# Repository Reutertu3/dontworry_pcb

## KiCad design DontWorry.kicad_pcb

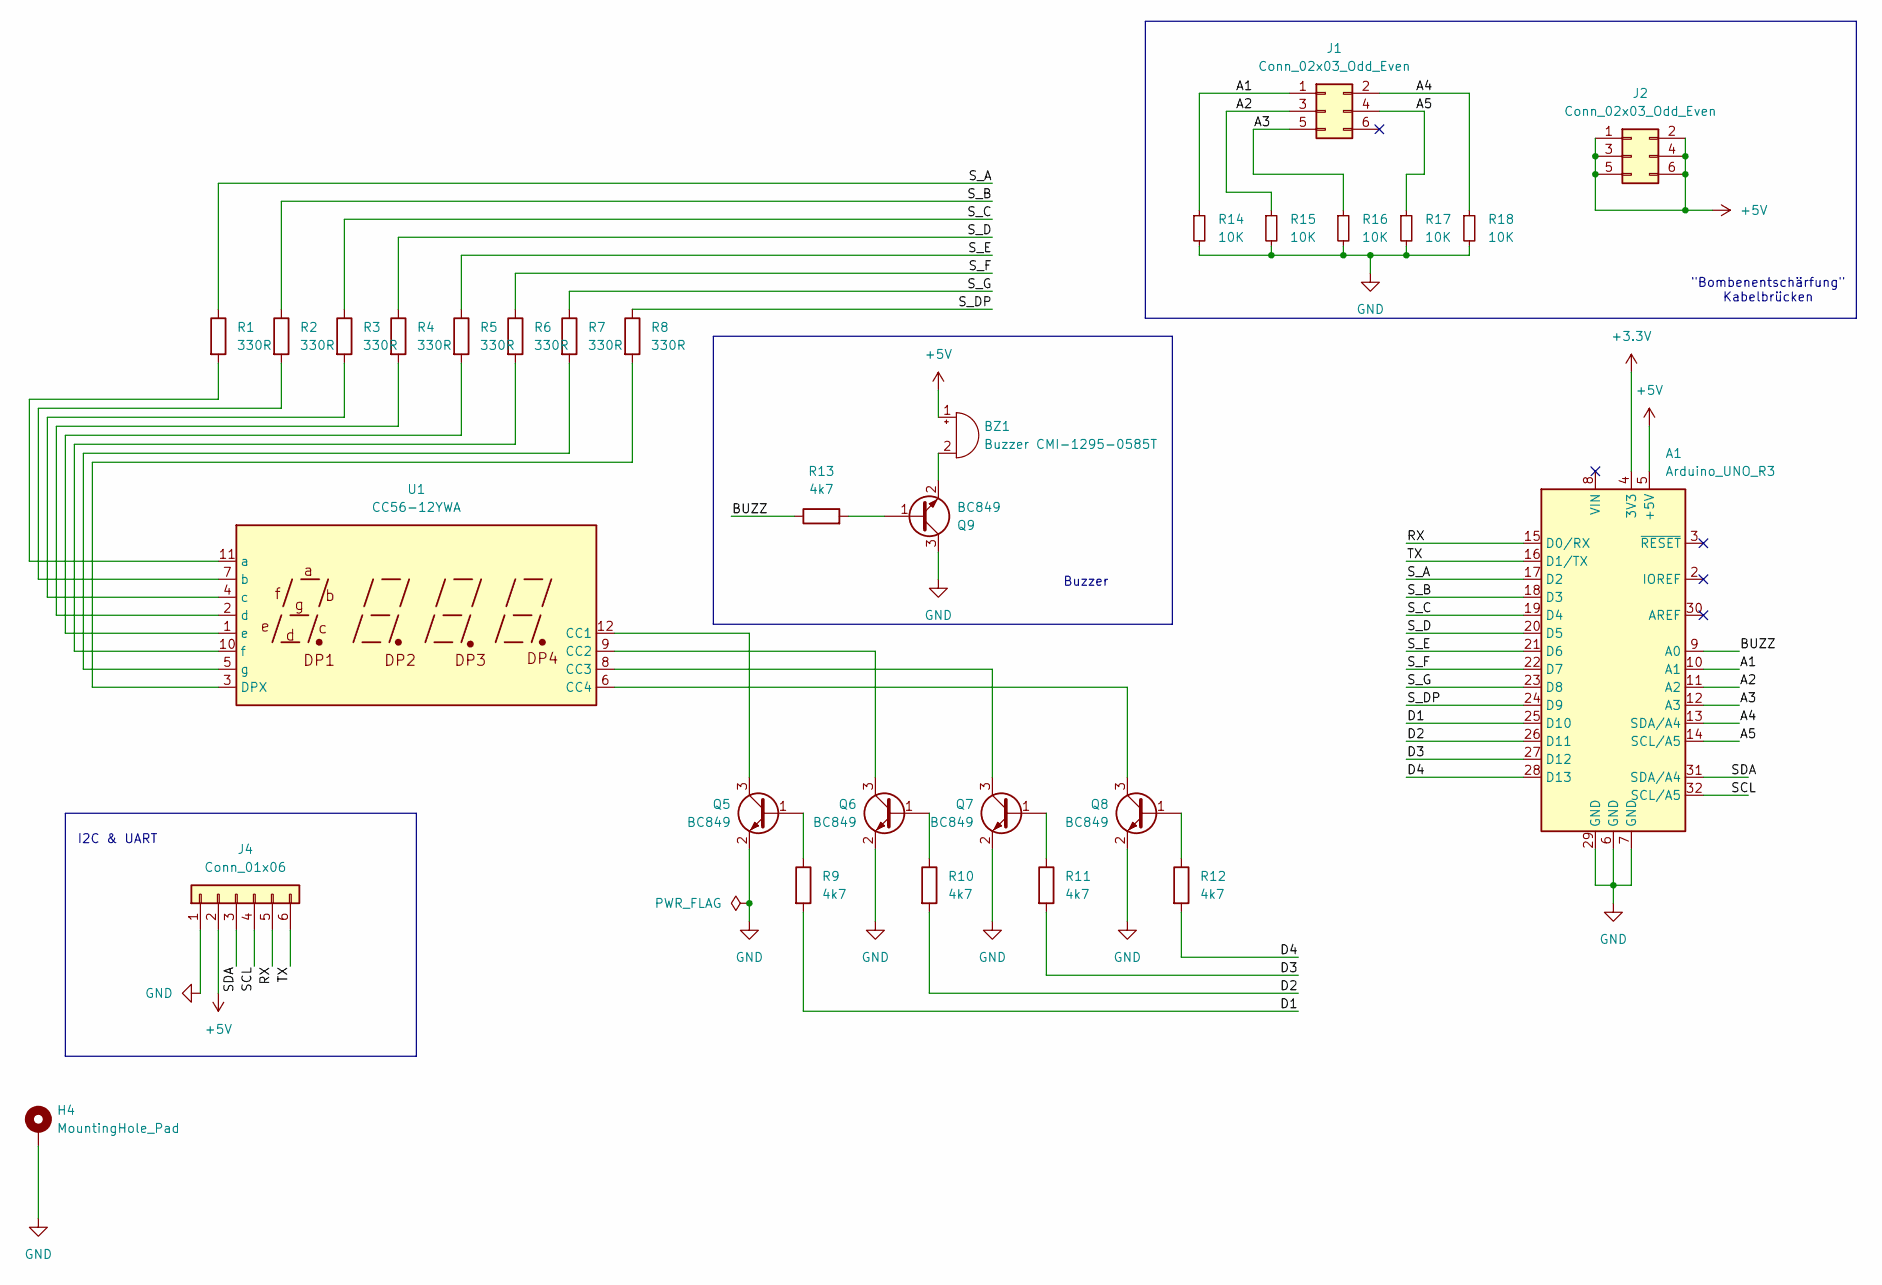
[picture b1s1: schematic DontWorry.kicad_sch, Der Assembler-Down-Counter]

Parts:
A1: Arduino_UNO_R3
BZ1: Buzzer CMI-1295-0585T; Buzzer_12x9.5RM7.6
H4: MountingHole_Pad; MountingHole_3.2mm_M3_DIN965_Pad
J1, J2: Conn_02x03_Odd_Even; PinHeader_2x03_P2.54mm_Vertical
J4: Conn_01x06; PinHeader_2x03_P2.54mm_Vertical
Q5, Q6, Q7, Q8, Q9: BC849; SOT-23
R1, R2, R3, R4, R5, R6, R7, R8: 330R; R_0805_2012Metric
R9, R10, R11, R12, R13: 4k7; R_0805_2012Metric
R14, R15, R16, R17, R18: 10K; R_0805_2012Metric
U1: CC56-12YWA

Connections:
+3.3V: A1.4 (3V3)
+5V: A1.5 (+5V), BZ1.1 (+), J2.1, J2.2, J2.3, J2.4, J2.5, J2.6, J4.2
/A1: A1.10 (A1), J1.1, R14.1
/A2: A1.11 (A2), J1.3, R15.1
/A3: A1.12 (A3), J1.5, R16.1
/A4: A1.13 (SDA/A4), J1.2, R18.1
/A5: A1.14 (SCL/A5), J1.4, R17.1
/BUZZ: A1.9 (A0), R13.1
/D1: A1.25 (D10), R9.2
/D2: A1.26 (D11), R10.2
/D3: A1.27 (D12), R11.2
/D4: A1.28 (D13), R12.2
/RX: A1.15 (D0/RX), J4.5
/SCL: A1.32 (SCL/A5), J4.4
/SDA: A1.31 (SDA/A4), J4.3
/S_A: A1.17 (D2), R1.1
/S_B: A1.18 (D3), R2.1
/S_C: A1.19 (D4), R3.1
/S_D: A1.20 (D5), R4.1
/S_DP: A1.24 (D9), R8.1
/S_E: A1.21 (D6), R5.1
/S_F: A1.22 (D7), R6.1
/S_G: A1.23 (D8), R7.1
/TX: A1.16 (D1/TX), J4.6
GND: A1.6 (GND), A1.7 (GND), A1.29 (GND), H4.1, J4.1, Q5.2 (E), Q6.2 (E), Q7.2 (E), Q8.2 (E), Q9.3 (C), R14.2, R15.2, R16.2, R17.2, R18.2
unnamed: BZ1.2 (-), Q9.2 (E)
unnamed: Q5.1 (B), R9.1
unnamed: Q5.3 (C), U1.12 (CC1)
unnamed: Q6.1 (B), R10.1
unnamed: Q6.3 (C), U1.9 (CC2)
unnamed: Q7.1 (B), R11.1
unnamed: Q7.3 (C), U1.8 (CC3)
unnamed: Q8.1 (B), R12.1
unnamed: Q8.3 (C), U1.6 (CC4)
unnamed: Q9.1 (B), R13.2
unnamed: R8.2, U1.3 (DPX)
unnamed: R1.2, U1.11 (a)
unnamed: R2.2, U1.7 (b)
unnamed: R3.2, U1.4 (c)
unnamed: R4.2, U1.2 (d)
unnamed: R5.2, U1.1 (e)
unnamed: R6.2, U1.10 (f)
unnamed: R7.2, U1.5 (g)

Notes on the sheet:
Buzzer
I2C & UART
"Bombenentschärfung" Kabelbrücken

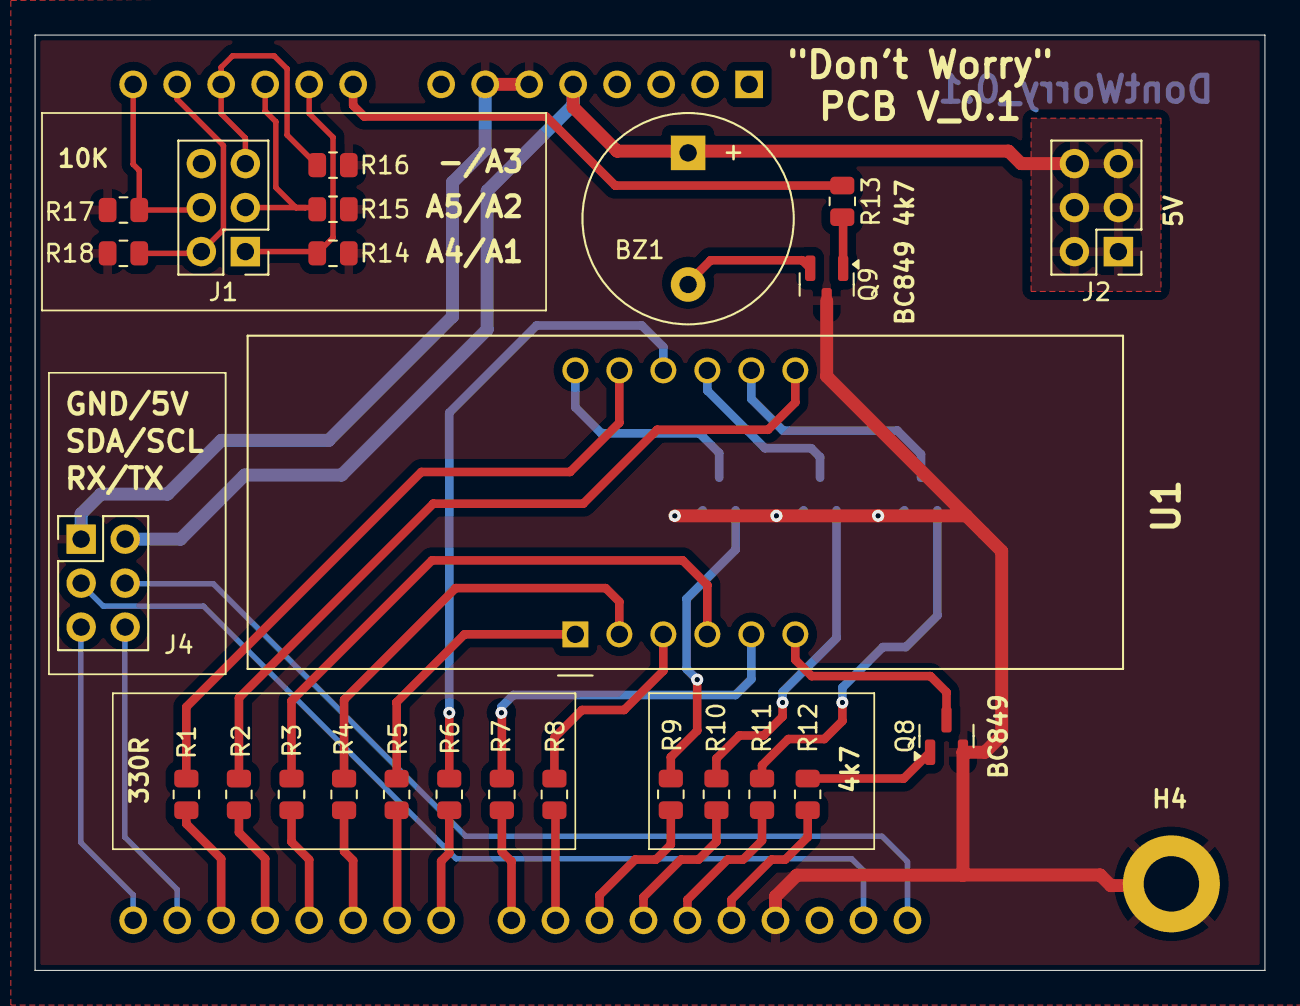
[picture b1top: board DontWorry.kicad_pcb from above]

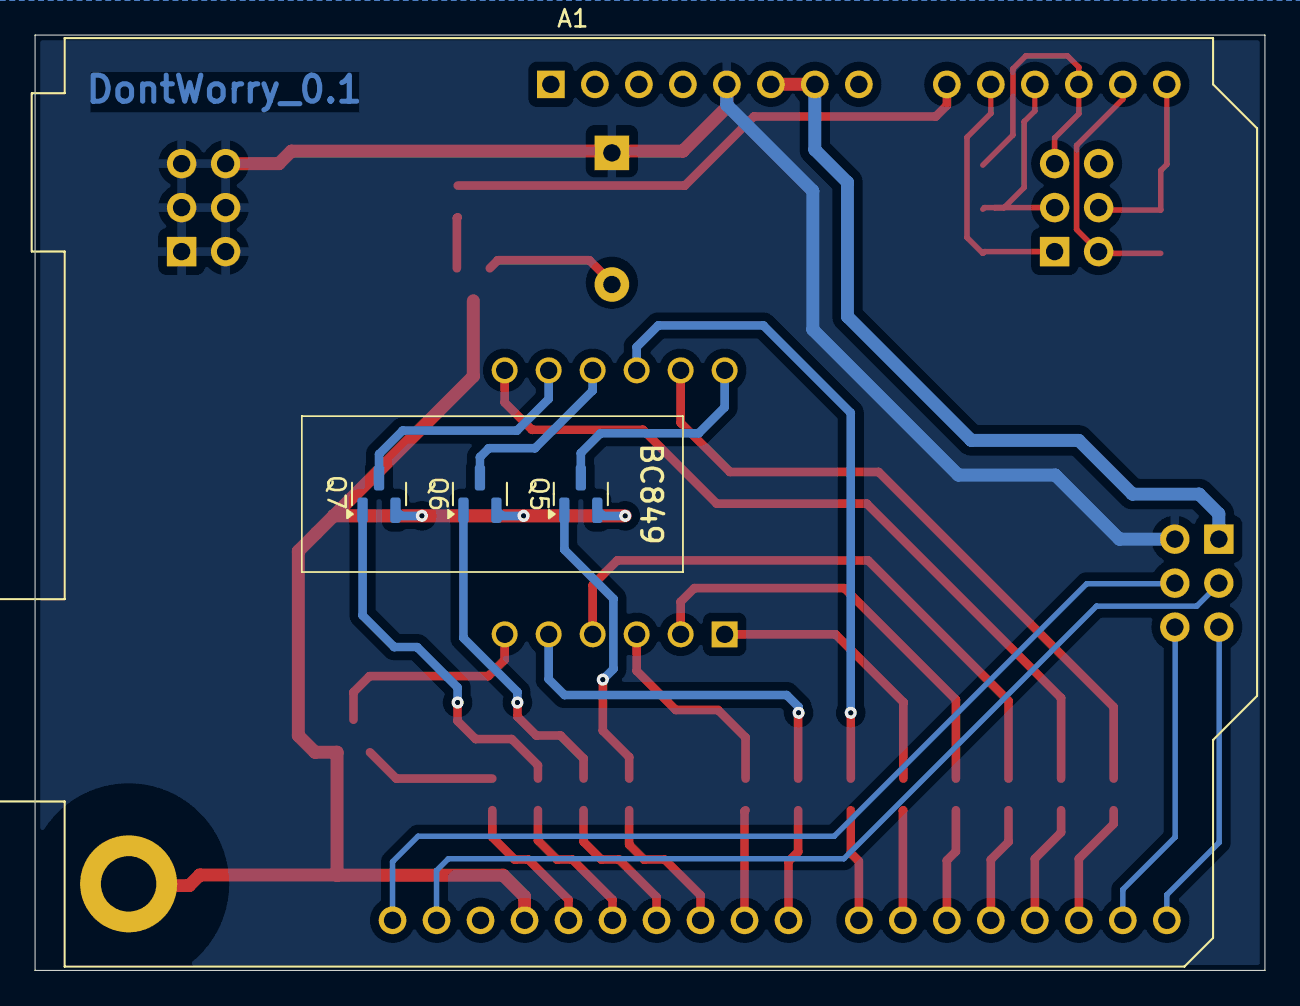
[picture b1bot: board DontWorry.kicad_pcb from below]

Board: 2 copper layers, 71.0 x 54.0 mm, 30 parts (4 on the bottom side), 42 nets.

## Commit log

2024-10-02 Init
2024-10-06 Updated PCB
2024-10-07 Added bottom GND fill
2024-10-07 Added more descriptions on Silk
2024-10-07 Updated traces and Silk style
2024-10-07 Increased GND hole pad clearance
2024-10-07 Added pad clearance
2024-10-07 New image
2024-10-07 Moved Buzzer south for increased pin clearance
